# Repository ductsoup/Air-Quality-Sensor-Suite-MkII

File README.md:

# Air-Quality-Sensor-Suite-MkII
A simple, inexpensive but accurate air quality monitor built around a Raspberry Pi 3 or Pi Zero W with the ability to inteface with industrial SCADA systems via Modbus TCP. With a few additional lines of code in the main loop it's relatively straightfoward to push the entire collected and calculated data set to an IoT/IIoT MQTT broker.

The two attached sensors read temperature, pressure, humidity, VOC and particulates. The script then derives other quantities such as dewpoint, air density, air quality index (AQI), NowCast and indoor air quality (IAQ).

## Usage Notes
While tested on Raspian Jessie and Python3 it will probably run on older versions of Python or newer versions of Raspbian with little or no modification.

```sudo python3 main.py```

By default the Modbus slave binds to all active connections. Root privledges are
requred because we're serving on the Modbus default port 502.

As a practical matter you'll probably want to set this script up to run as a service 
with systemd rather than using cron or rc.local. 

* https://www.raspberrypi.org/documentation/linux/usage/systemd.md
* https://github.com/joan2937/pigpio/tree/master/util

## Requirements

### Modbus-tk
https://github.com/ljean/modbus-tk

This provides the MODBUS TCP transport. Values are mapped into holding registeres encoded as an [IEEE 754 32-bit float](https://en.wikipedia.org/wiki/IEEE_754).

If you'd like to send the data to an MQTT broker instead just install Paho and modify the relevant sections in ```main.py```.

### Pigpio
http://abyz.me.uk/rpi/pigpio/index.html

This is used to bitbang GPIO 18 to interface with the PMS5003, just pick another pin if that's inconvenient. 

### Pimoroni BME680
https://github.com/pimoroni/bme680

I'm using an Adafruit breakout board with the Pimoroni library for their breakout board. Both boards are functionally identical, the only relevant difference between them (other than the pinouts) is the default I2C address so I need to specify that when I create the instance.

```bme680.BME680(i2c_addr=0x77)```

## Sensors/Interfaces
### BME680 (I2C) 
* [datasheet](https://cdn-shop.adafruit.com/product-files/3660/BME680.pdf)
* https://shop.pimoroni.com/products/bme680
* https://www.adafruit.com/product/3660

### PMS5003 (software serial)
* [datasheet](https://cdn-shop.adafruit.com/product-files/3686/plantower-pms5003-manual_v2-3.pdf)
* https://www.adafruit.com/product/3686

The original design used a PPD42NS or SM-PWM-01A particle sensor which was difficult to interface with anything but an embedded device because you really need hardware interrupts to count the particles in real time. The PMS5003 does all that internally, reports in engineering units and provides a 3.3V compatible serial output making it very easy to interface with a Raspberry Pi.

## MODBUS Register Map
### System
```
40001   Quality Control (3.14159265359)
```
### Measured BME680
```
40003   Temperature (C)
40005   Temperature (F)
40007   Pressure (hPa)
40009   Pressure (inHg)
40011   Relative Humidity (%)
40013   VOC (kOhm)
```
### Measured PMS5003
```
40015   PM1.0 standard (ug/m3)
40017   PM2.5 standard (ug/m3)
40019   PM10 standard (ug/m3)
40021   PM1.0 environmental (ug/m3)
40023   PM2.5 environmental (ug/m3)
40025   PM10 environmental (ug/m3)
40027   Particles > 0.3 um / 0.1L air
40029   Particles > 0.5 um / 0.1L air
40031   Particles > 1.0 um / 0.1L air
40033   Particles > 2.5 um / 0.1L air
40035   Particles > 5.0 um / 0.1L air
40037   Particles > 50  um / 0.1L air
```
### Derived
```
40039   Dewpoint (C)
40041   Dewpoint (F)
40043   Partial pressure water vapor (hPa)
40045   Partial pressure dry air (hPa)
40047   Air density (kg/m3)
40049   Air density (lb/ft3)

40051   AQI (0-500, -1 if unavailable)
40053   PM25 contribution to AQI
40055   PM10 contribution to AQI
40057   AQI NowCast
40059   PM25 contribution to AQI NowCast
40061   PM10 contribution to AQI NowCast
40063   AQI Current (1 minute)
40065   PM25 contribution to AQI Current
40067   PM10 contribution to AQI Current

40069   PM01 60 second average (ug/m3)
40071   PM01 60 minute average (ug/m3)
40073   PM01 24 hour average (ug/m3)
40075   PM25 60 second average (ug/m3)
40077   PM25 60 minute average (ug/m3)
40079   PM25 24 hour average (ug/m3)
40081   PM10 60 second average (ug/m3)
40083   PM10 60 minute average (ug/m3)
40085   PM10 24 hour average (ug/m3)

40087   IAQ (0-100, -1 if unavailable)
40089   RH contribution to IAQ
40091   VOC contribution to IAQ
40093   VOC 60 second average (kOhm)
40095   VOC 60 minute average (kOhm)
40097   VOC 24 hour average (kOhm)
```
## Classes
### Unit Conversion
Weather calculations are notorious for mixing SI and imperial units and combining constants making them difficult to follow. Even with SI it's not uncommon to switch back and forth between units like Celsius and Kelvin.

To simplify, pass an SI value (Celsius) when you initialize a unit conversion object. You can then retrieve the value in any relavant unit, SI or imperial (Celsius, Kelvin, Fahrenheit or Rankine).

```python
Temperature = T(25)
print(Temperature.C, Temperature.K, Temperature.F, Temperature.R)
```
There are also unit conversion classes for pressure and density.

### Cascadable Running/Retained Average 
The first challenge is that AQI requires a 24 hour average measurement and embedded systems can rest at any time. The second is if you're sampling at 1 second intervals that's 86400 (60*60*24) samples to average.

This class allows you to define a one second sample aggregated to a one minute average, cascaded to a one hour average, cascaded to a one day average (lather, rise and repeat for weekly, monthly or annual), writing the results to storage and reloading as necessary between resets. In the 24 hour example it only retains 144 values (60+60+24). As you're building history to whatever average you've defined, the class will provide the best approximation available.

The caveat with SD storage is you have a finite number of write cycles. To start I've chosen the compromise of writing hourly. If the reset is short duration, it won't significantly compromise the results. 

```python
pm25_24h = CRR_AVG(24, jfile = "pm25_24h")    # daily average (retained)
pm25_60m = CRR_AVG(60, pm25_24h)              # hourly average
pm25_60s = CRR_AVG(60, pm25_60m)              # minutely average
```

### Derived Weather Variables
This class approximates dewpoint and air density from the BME680 observations.

### AQI Air Quality Index and NowCast
The AQI class implments [Air Quality Index](https://en.wikipedia.org/wiki/Air_quality_index) and 
[NowCast](https://en.wikipedia.org/wiki/NowCast_(air_quality_index)) calculations. Not defined in those standards but useful for what I'm doing I've also implemented a one minute AQI. 

Currently the class implements only the PM2.5 and PM10 components of AQI. It is however, designed to be easily extended to include O3, CO, SO2 and No2.

### IAQ Indoor Air Quality
There isn't a generally accepted standard for indoor air quality that I am aware of however, Bosch has provided a closed source binary called [BSEC](https://www.bosch-sensortec.com/bst/products/all_products/BSEC) for use with the BME680 to do that calculation. Based on the description in the datasheet they're likely doing something similar to what is implemented in the IAQ class. 

## Enclosure
For the enclosure I customized [The Ultimate box maker](https://www.thingiverse.com/thing:1264391) from Thingiverse.

My 3D printer didn't do such a good job on the 2.05mm tap drill holes for mounting the Pi Zero W and I'm guessing most others won't either so I opened those up with a 5/64 (1.98mm) drill, ran a M2.5x0.45 tap through by hand then finished up with some M2.5 nylon screws (Amazon is your friend for fine tools and supplies like this).

## Rev 1 10/09/2018
I added support for the SGP30 VOC and eCO2 sensor.

### SGP30 (I2C) 
* [datasheet](https://cdn-learn.adafruit.com/assets/assets/000/050/058/original/Sensirion_Gas_Sensors_SGP30_Datasheet_EN.pdf)
* https://www.adafruit.com/product/3709

I also added Eagle files for a custom Pi Hat which I've built a couple times so it's verified good (Sunstone).

The perma-proto board construction above works great but it's a little tedious and somewhat error prone to build. Populating the custom PCB is easy. It's actually taking far longer to 3D print the enclosure than do the build and configure the software on the Pi Zero W.

```
40099   CO2 equivalent (ppm)
40101   CO2 equivalent 60 second average (ppm)
40103   CO2 equivalent 60 minute average (ppm)
40105   CO2 equivalent 24 hour average (ppm)
40107   VOC (ppb)
40109   VOC 60 second average (ppb)
40111   VOC 60 minute average (ppb)
40113   VOC 24 hour average (ppb)  
40115   Absolute Humidity (g/m^3)
```

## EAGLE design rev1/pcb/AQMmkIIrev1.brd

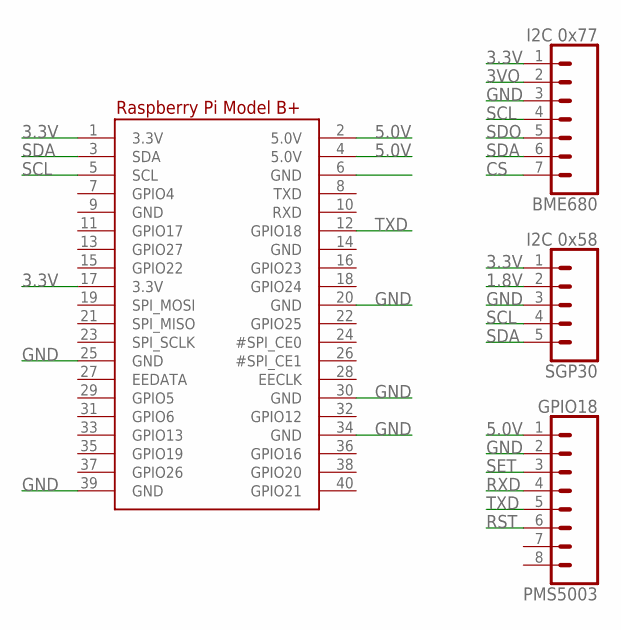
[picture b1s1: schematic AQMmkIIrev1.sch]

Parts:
BME680: I2C 0x77; 1X07
PMS5003: GPIO18; 1X08
RPI1: RASPBERRYPI_BPLUS_BONNETNODIM; PI_BONNET_NODIM
SGP30: I2C 0x58; 1X05

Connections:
1.8V: SGP30.2
3.3V: BME680.1, RPI1.1 (3.3V), RPI1.17 (3.3V), SGP30.1
3VO: BME680.2
5.0V: PMS5003.1, RPI1.2 (5.0V), RPI1.4 (5.0V)
CS: BME680.7
GND: BME680.3, PMS5003.2, RPI1.6 (GND), RPI1.9 (GND), RPI1.14 (GND), RPI1.20 (GND), RPI1.25 (GND), RPI1.30 (GND), RPI1.34 (GND), RPI1.39 (GND), SGP30.3
RST: PMS5003.6
RXD: PMS5003.4
SCL: BME680.4, RPI1.5 (SCL), SGP30.4
SDA: BME680.6, RPI1.3 (SDA), SGP30.5
SDO: BME680.5
SET: PMS5003.3
TXD: PMS5003.5, RPI1.12 (GPIO18)

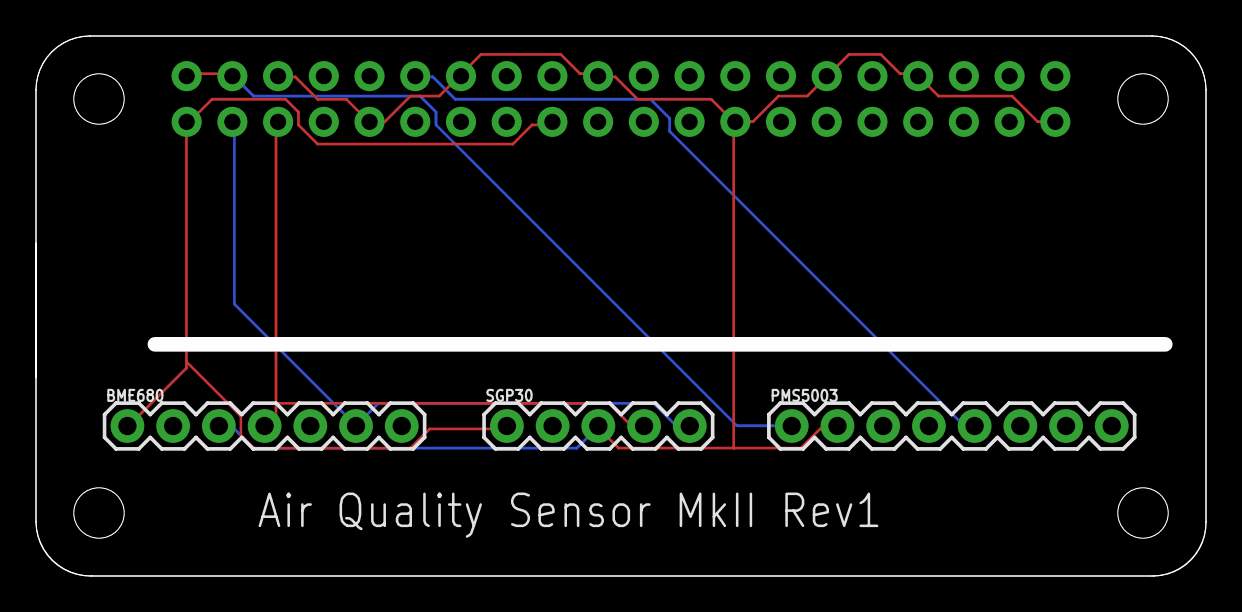
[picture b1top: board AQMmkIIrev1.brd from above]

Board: 2 copper layers, 64.2 x 29.2 mm, 4 parts (0 on the bottom side), 6 nets.

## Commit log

2018-01-24 Update LICENSE
2018-01-25 IPL1
2018-01-28 enclosure
2018-07-10 Added examples
2018-09-14 Added support for MQTT
2018-10-09 rev1
    Added PCB and support for SGP30
2018-10-09 documentation update
2018-10-09 build notes
2019-01-06 software update
2019-01-07 Corrected MODBUS configuration and added comments

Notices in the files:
parts and their libraries:
microbuilder: This work is placed in the public domain, and may be freely used for commercial and non-commercial work with the following conditions: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
SparkFun-Connectors: Licensing: Creative Commons ShareAlike 4.0 International - https://creativecommons.org/licenses/by-sa/4.0
